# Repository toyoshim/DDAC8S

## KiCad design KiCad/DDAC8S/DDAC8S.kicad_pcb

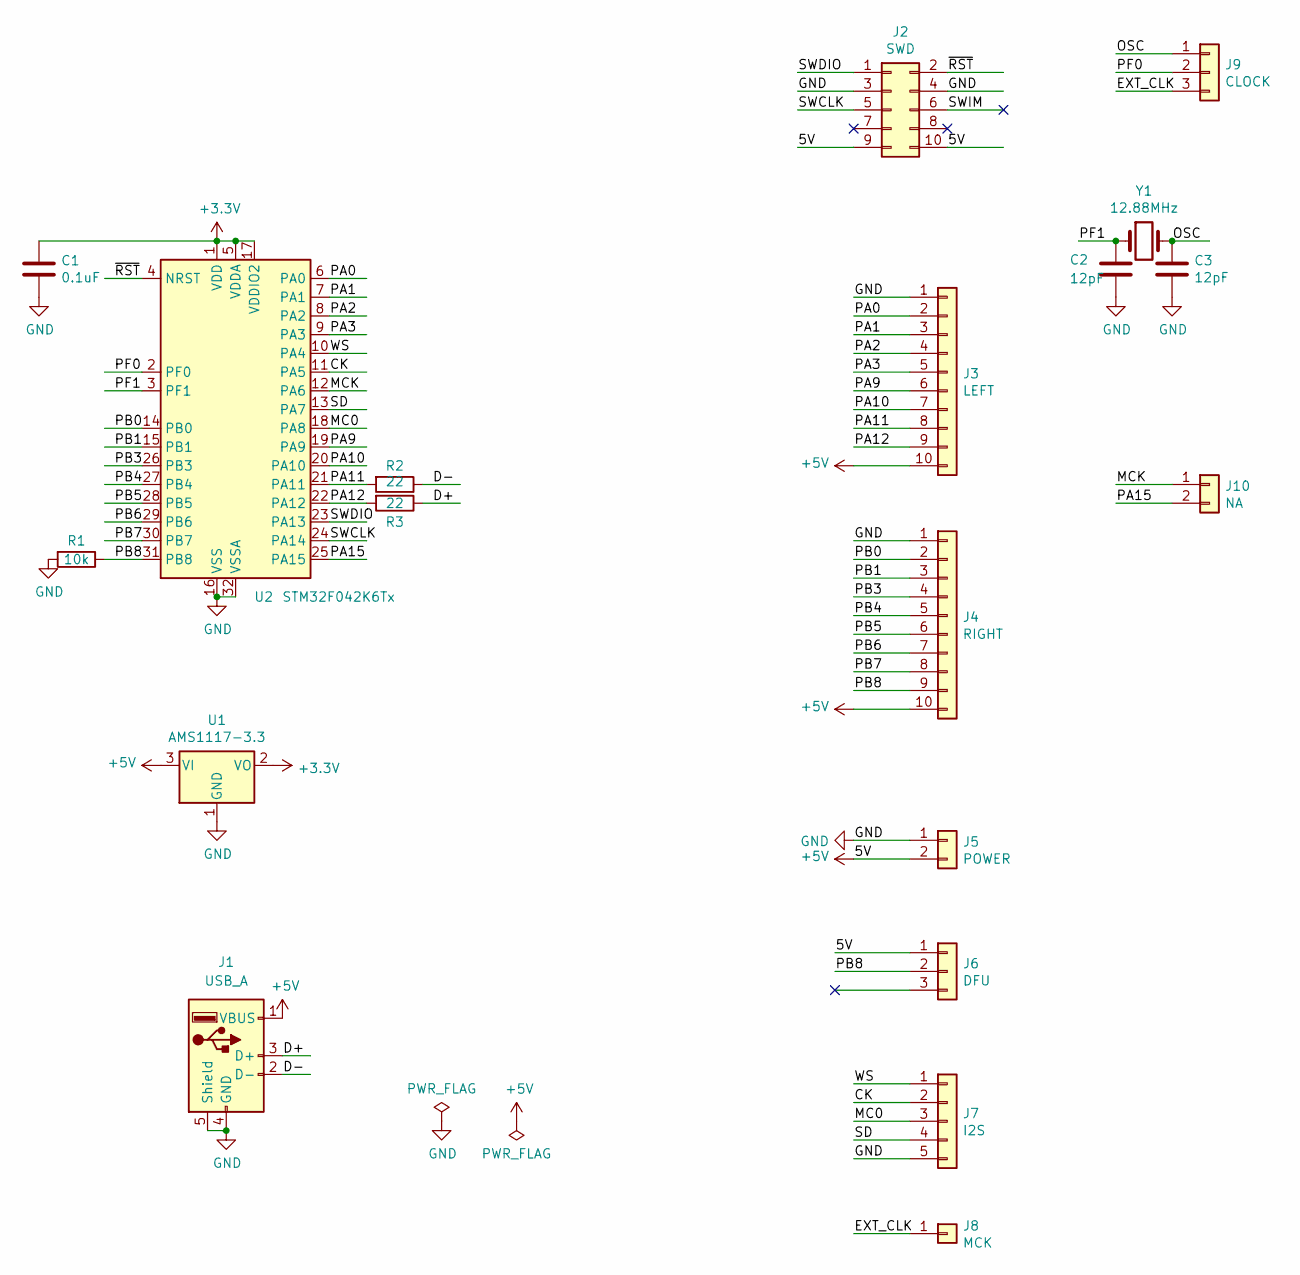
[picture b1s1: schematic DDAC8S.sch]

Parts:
C1: 0.1uF; C_0603_1608Metric
C2, C3: 12pF; C_0603_1608Metric
J1: USB_A; USB_TypeA_Edge
J2: SWD; PinHeader_2x05_P2.54mm_Vertical
J3: LEFT; PinHeader_1x10_P2.54mm_Vertical
J4: RIGHT; PinHeader_1x10_P2.54mm_Vertical
J5: POWER; PinHeader_1x02_P2.54mm_Vertical
J6: DFU; PinHeader_1x03_P2.54mm_Vertical
J7: I2S; PinHeader_1x05_P2.54mm_Vertical
J8: MCK; PinHeader_1x01_P2.54mm_Vertical
J9: CLOCK; PinHeader_1x03_P2.54mm_Vertical
J10: NA; PinHeader_1x02_P2.54mm_Vertical
R1: 10k; R_0603_1608Metric
R2, R3: 22; R_0603_1608Metric
U1: AMS1117-3.3; SOT-223-3_TabPin2
U2: STM32F042K6Tx; LQFP-32_7x7mm_P0.8mm
Y1: 12.88MHz; Crystal_HC49-U_Vertical

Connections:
+3V3: C1.1, U1.2 (VO), U2.1 (VDD), U2.5 (VDDA), U2.17 (VDDIO2)
+5V: J1.1 (VBUS), J2.9, J2.10, J3.10, J4.10, J5.2, J6.1, U1.3 (VI)
/CK: J7.2, U2.11 (PA5)
/D+: J1.3 (D+), R3.1
/D-: J1.2 (D-), R2.1
/EXT_CLK: J8.1, J9.3
/MC0: J7.3, U2.18 (PA8)
/MCK: J10.1, U2.12 (PA6)
/OSC: C3.1, J9.1, Y1.2
/PA0: J3.2, U2.6 (PA0)
/PA1: J3.3, U2.7 (PA1)
/PA2: J3.4, U2.8 (PA2)
/PA3: J3.5, U2.9 (PA3)
/PA9: J3.6, U2.19 (PA9)
/PA10: J3.7, U2.20 (PA10)
/PA11: J3.8, R2.2, U2.21 (PA11)
/PA12: J3.9, R3.2, U2.22 (PA12)
/PA15: J10.2, U2.25 (PA15)
/PB0: J4.2, U2.14 (PB0)
/PB1: J4.3, U2.15 (PB1)
/PB3: J4.4, U2.26 (PB3)
/PB4: J4.5, U2.27 (PB4)
/PB5: J4.6, U2.28 (PB5)
/PB6: J4.7, U2.29 (PB6)
/PB7: J4.8, U2.30 (PB7)
/PB8: J4.9, J6.2, R1.1, U2.31 (PB8)
/PF0: J9.2, U2.2 (PF0)
/PF1: C2.1, U2.3 (PF1), Y1.1
/SD: J7.4, U2.13 (PA7)
/SWCLK: J2.5, U2.24 (PA14)
/SWDIO: J2.1, U2.23 (PA13)
/WS: J7.1, U2.10 (PA4)
/~RST: J2.2, U2.4 (NRST)
GND: C1.2, C2.2, C3.2, J1.4 (GND), J1.5 (Shield), J2.3, J2.4, J3.1, J4.1, J5.1, J7.5, R1.2, U1.1 (GND), U2.16 (VSS), U2.32 (VSSA)

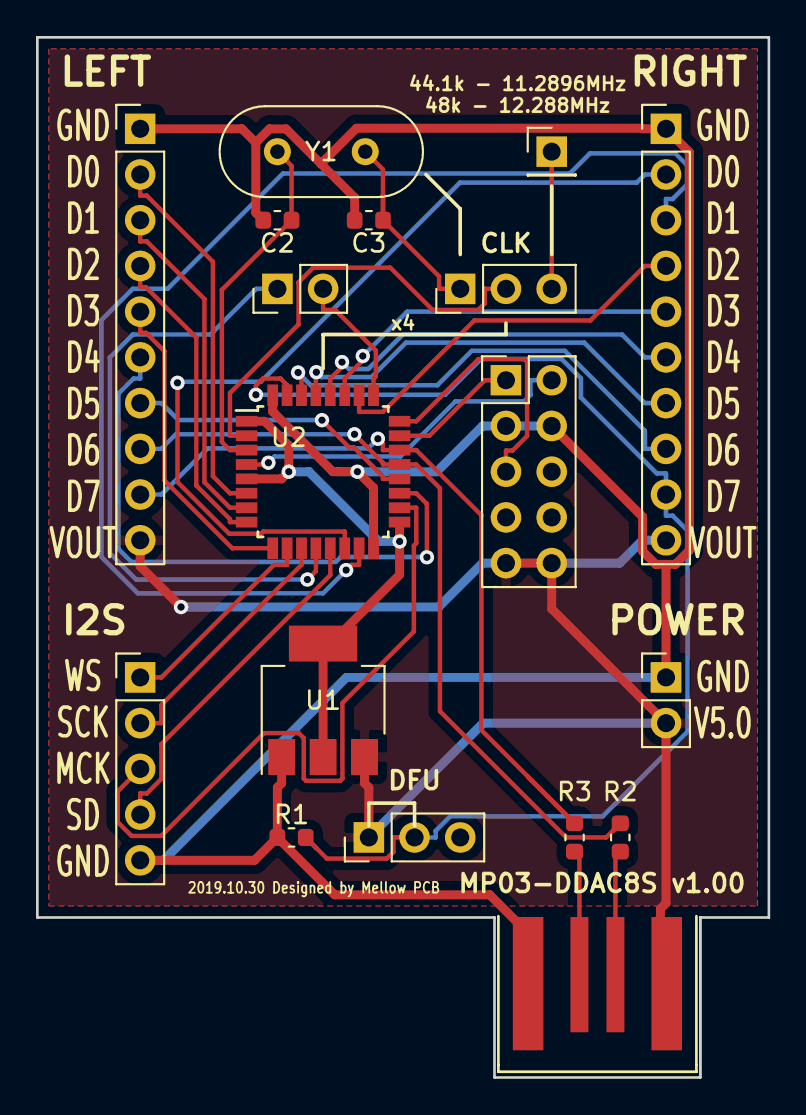
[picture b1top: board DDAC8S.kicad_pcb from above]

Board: 2 copper layers, 40.6 x 57.8 mm, 19 parts (1 on the bottom side), 34 nets.

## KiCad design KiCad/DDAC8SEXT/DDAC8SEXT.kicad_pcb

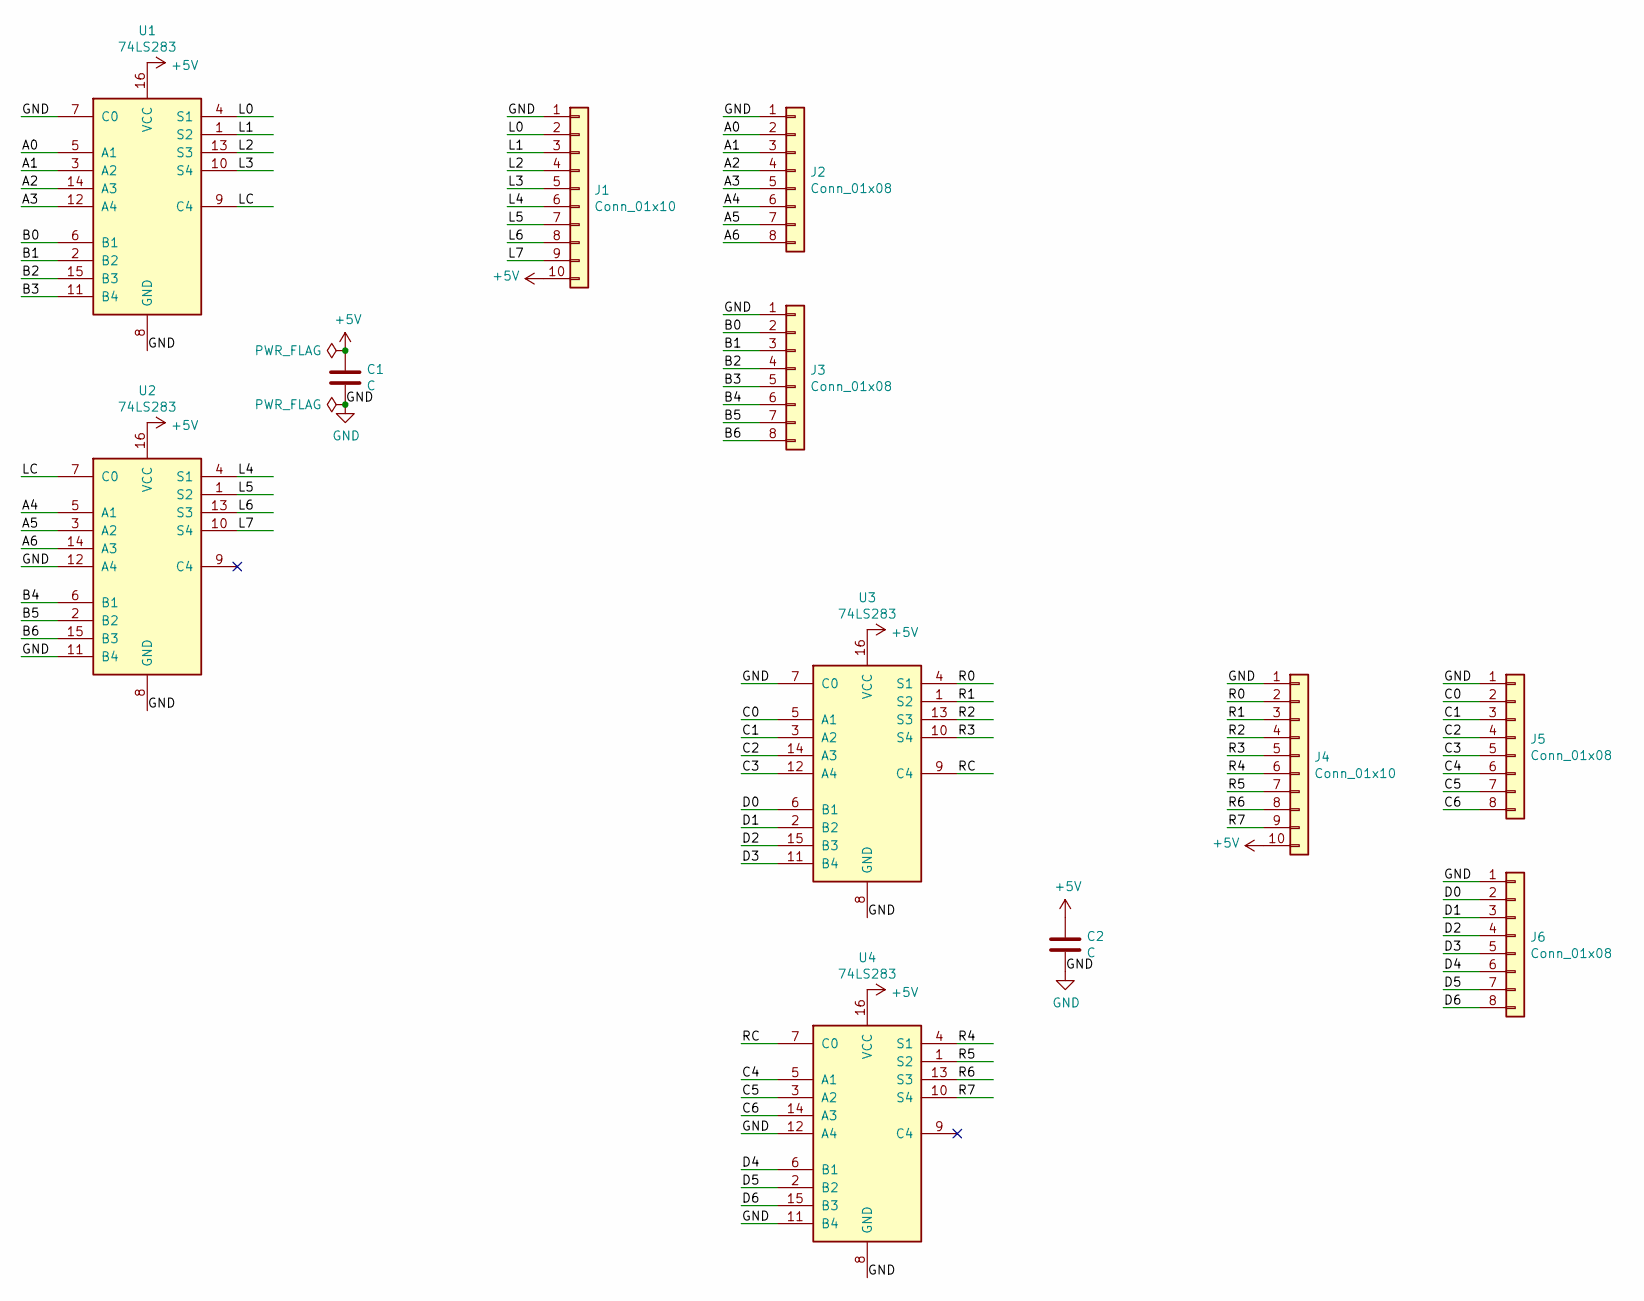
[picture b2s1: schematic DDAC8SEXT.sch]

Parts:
C1, C2: C; C_Disc_D3.0mm_W1.6mm_P2.50mm
J1, J4: Conn_01x10; PinSocket_1x10_P2.54mm_Vertical
J2, J3, J5, J6: Conn_01x08; PinHeader_1x08_P2.54mm_Vertical
U1, U2, U3, U4: 74LS283; DIP-16_W7.62mm

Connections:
+5V: C1.1, C2.1, J1.10, J4.10, U1.16 (VCC), U2.16 (VCC), U3.16 (VCC), U4.16 (VCC)
/A0: J2.2, U1.5 (A1)
/A1: J2.3, U1.3 (A2)
/A2: J2.4, U1.14 (A3)
/A3: J2.5, U1.12 (A4)
/A4: J2.6, U2.5 (A1)
/A5: J2.7, U2.3 (A2)
/A6: J2.8, U2.14 (A3)
/B0: J3.2, U1.6 (B1)
/B1: J3.3, U1.2 (B2)
/B2: J3.4, U1.15 (B3)
/B3: J3.5, U1.11 (B4)
/B4: J3.6, U2.6 (B1)
/B5: J3.7, U2.2 (B2)
/B6: J3.8, U2.15 (B3)
/C0: J5.2, U3.5 (A1)
/C1: J5.3, U3.3 (A2)
/C2: J5.4, U3.14 (A3)
/C3: J5.5, U3.12 (A4)
/C4: J5.6, U4.5 (A1)
/C5: J5.7, U4.3 (A2)
/C6: J5.8, U4.14 (A3)
/D0: J6.2, U3.6 (B1)
/D1: J6.3, U3.2 (B2)
/D2: J6.4, U3.15 (B3)
/D3: J6.5, U3.11 (B4)
/D4: J6.6, U4.6 (B1)
/D5: J6.7, U4.2 (B2)
/D6: J6.8, U4.15 (B3)
/L0: J1.2, U1.4 (S1)
/L1: J1.3, U1.1 (S2)
/L2: J1.4, U1.13 (S3)
/L3: J1.5, U1.10 (S4)
/L4: J1.6, U2.4 (S1)
/L5: J1.7, U2.1 (S2)
/L6: J1.8, U2.13 (S3)
/L7: J1.9, U2.10 (S4)
/LC: U1.9 (C4), U2.7 (C0)
/R0: J4.2, U3.4 (S1)
/R1: J4.3, U3.1 (S2)
/R2: J4.4, U3.13 (S3)
/R3: J4.5, U3.10 (S4)
/R4: J4.6, U4.4 (S1)
/R5: J4.7, U4.1 (S2)
/R6: J4.8, U4.13 (S3)
/R7: J4.9, U4.10 (S4)
/RC: U3.9 (C4), U4.7 (C0)
GND: C1.2, C2.2, J1.1, J2.1, J3.1, J4.1, J5.1, J6.1, U1.7 (C0), U1.8 (GND), U2.8 (GND), U2.11 (B4), U2.12 (A4), U3.7 (C0), U3.8 (GND), U4.8 (GND), U4.11 (B4), U4.12 (A4)

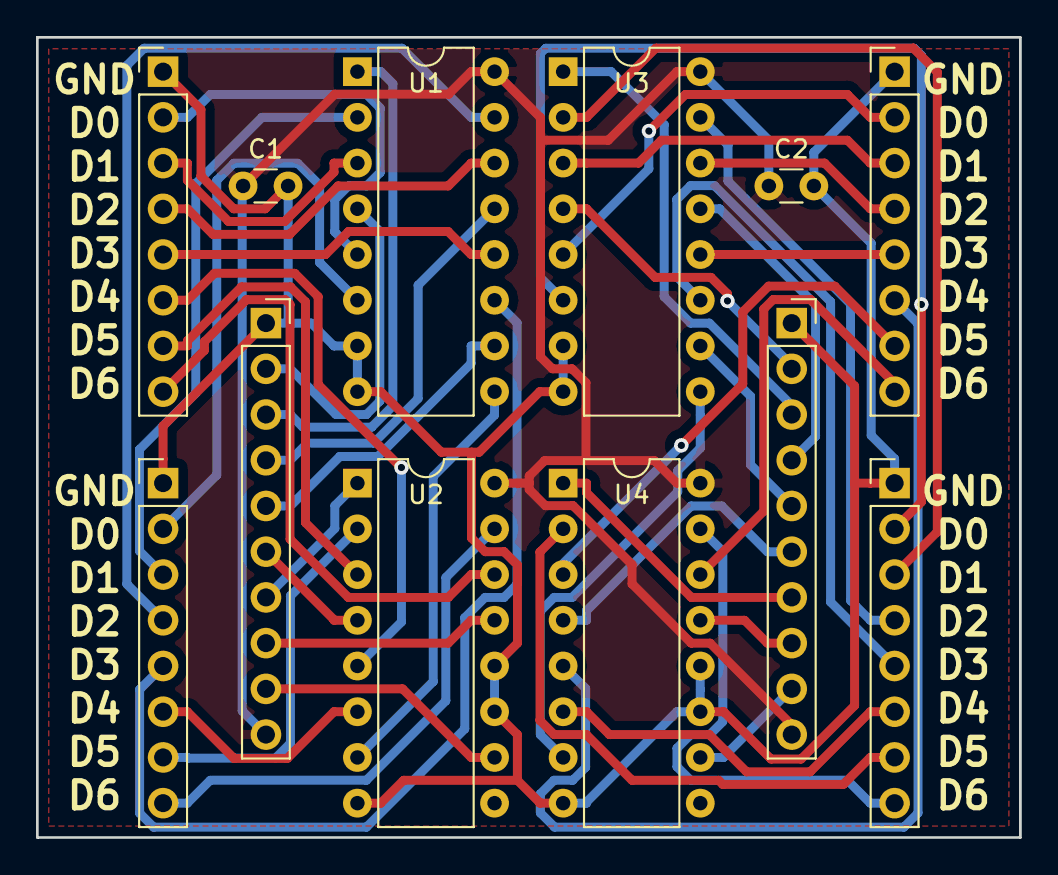
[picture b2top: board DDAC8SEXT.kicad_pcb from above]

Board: 2 copper layers, 54.6 x 44.4 mm, 12 parts (0 on the bottom side), 48 nets.

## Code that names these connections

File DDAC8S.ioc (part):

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Mcu.Name=STM32F042K(4-6)Tx
Mcu.Package=LQFP32
Mcu.UserName=STM32F042K6Tx
PA0.GPIOParameters=GPIO_PuPd,GPIO_Label
PA0.GPIO_Label=L0
PA0.GPIO_PuPd=GPIO_PULLDOWN
PA0.Signal=GPIO_Input
PA1.GPIOParameters=GPIO_PuPd,GPIO_Label
PA1.GPIO_Label=L1
PA1.GPIO_PuPd=GPIO_PULLDOWN
PA1.Signal=GPIO_Input
PA10.GPIOParameters=GPIO_PuPd,GPIO_Label
PA10.GPIO_Label=L5
PA10.GPIO_PuPd=GPIO_PULLDOWN
PA10.Signal=GPIO_Input
PA11.GPIOParameters=GPIO_PuPd,GPIO_Label
PA11.GPIO_Label=L6
PA11.GPIO_PuPd=GPIO_PULLDOWN
PA11.Signal=GPIO_Input
PA12.GPIOParameters=GPIO_PuPd,GPIO_Label
PA12.GPIO_Label=L7
PA12.GPIO_PuPd=GPIO_PULLDOWN
PA12.Signal=GPIO_Input
PA13.Mode=Serial_Wire
PA13.Signal=SYS_SWDIO
PA14.Mode=Serial_Wire
PA14.Signal=SYS_SWCLK
PA2.GPIOParameters=GPIO_PuPd,GPIO_Label
PA2.GPIO_Label=L2
PA2.GPIO_PuPd=GPIO_PULLDOWN
PA2.Signal=GPIO_Input
PA3.GPIOParameters=GPIO_PuPd,GPIO_Label
PA3.GPIO_Label=L3
PA3.GPIO_PuPd=GPIO_PULLDOWN
PA3.Signal=GPIO_Input
PA4.Mode=Half_Duplex_Master
PA4.Signal=I2S1_WS
PA5.Mode=Half_Duplex_Master
PA5.Signal=I2S1_CK
PA6.Mode=Master_Clock_Activated
PA6.Signal=I2S1_MCK
PA7.Mode=Half_Duplex_Master
PA7.Signal=I2S1_SD
PA8.Mode=Clock-out
PA8.Signal=RCC_MCO
PA9.GPIOParameters=GPIO_PuPd,GPIO_Label
PA9.GPIO_Label=L4
PA9.GPIO_PuPd=GPIO_PULLDOWN
PA9.Signal=GPIO_Input
PB0.GPIOParameters=GPIO_PuPd,GPIO_Label
PB0.GPIO_Label=R0
PB0.GPIO_PuPd=GPIO_PULLDOWN
PB0.Signal=GPIO_Input
PB1.GPIOParameters=GPIO_PuPd,GPIO_Label
PB1.GPIO_Label=R1
PB1.GPIO_PuPd=GPIO_PULLDOWN
PB1.Signal=GPIO_Input
PB3.GPIOParameters=GPIO_PuPd,GPIO_Label
PB3.GPIO_Label=R2
PB3.GPIO_PuPd=GPIO_PULLDOWN
PB3.Signal=GPIO_Input
PB4.GPIOParameters=GPIO_PuPd,GPIO_Label
PB4.GPIO_Label=R3
PB4.GPIO_PuPd=GPIO_PULLDOWN
PB4.Signal=GPIO_Input
PB5.GPIOParameters=GPIO_PuPd,GPIO_Label
PB5.GPIO_Label=R4
PB5.GPIO_PuPd=GPIO_PULLDOWN
PB5.Signal=GPIO_Input
PB6.GPIOParameters=GPIO_PuPd,GPIO_Label
PB6.GPIO_Label=R5
PB6.GPIO_PuPd=GPIO_PULLDOWN
PB6.Signal=GPIO_Input
PB7.GPIOParameters=GPIO_PuPd,GPIO_Label
PB7.GPIO_Label=R6
PB7.GPIO_PuPd=GPIO_PULLDOWN
PB7.Signal=GPIO_Input
PB8.GPIOParameters=GPIO_PuPd,GPIO_Label
PB8.GPIO_Label=R7
PB8.GPIO_PuPd=GPIO_PULLDOWN
PB8.Signal=GPIO_Input
PF0-OSC_IN.Mode=HSE-External-Oscillator
PF0-OSC_IN.Signal=RCC_OSC_IN
PF1-OSC_OUT.Mode=HSE-External-Oscillator
PF1-OSC_OUT.Signal=RCC_OSC_OUT
RCC.HSE_VALUE=12288000
RCC.SYSCLKFreq_VALUE=49152000
RCC.SYSCLKSource=RCC_SYSCLKSOURCE_PLLCLK
board=custom

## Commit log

2020-04-13 initial
2020-04-13 Add firmware binary
2020-04-13 Add KiCad data
